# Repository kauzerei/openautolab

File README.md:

# OpenAutoLab

Free and open-source automatic film development machine.

[<br>Demo video](https://www.youtube.com/watch?v=Ryzbz89Sy8g)

OpenAutoLab is an attempt at making a cheap and simple film developing machine.
Inspired by Jobo Autolab, but cheaper, more repairable and open source.
Agitation is done by periodically moving fully submerged film, not rotating the drum constantly, so it is also more flexible, as it supports black-and-white processes.

Please take a look at the [OpenAutoLab documentation](https://kauzerei.github.io/openautolab/) for build and usage instructions.

- [Parts](https://kauzerei.github.io/openautolab/parts.html) contains information about all used electronic and mechanical components.
- [Build Instructions](https://kauzerei.github.io/openautolab/build_instructions.html) explains how to build the machine from scratch.
  - [Main Board](https://kauzerei.github.io/openautolab/main_board.html) concentrates on main board schematics and PCB layouts.
  - [Arduino Code](https://kauzerei.github.io/openautolab/arduino_code.html) contains build instructions for the source code of the controller of the machine.
- [Usage Instructions](https://kauzerei.github.io/openautolab/usage_instructions.html) explains how to use the finished machine.
- [Web Updater](https://kauzerei.github.io/openautolab/web_update.html) allows firmware upgrades on the main board.

You can find the latest released STL files and firmware binaries on the [GitHub releases page](https://github.com/kauzerei/openautolab/releases).

# Disclaimer

I do not take any responsibility for any damage done by mishandling chemicals.

For most processes rubber gloves suffice to keep you safe, but please refer to documents provided with each chemical you use, some are more toxic than others. This document explains the details of using the machine itself, without much attention towards the handling of chemicals. Research online if you are unsure, use your brain and be safe.

# License

The firmware, the design of 3d-printable files, the hardware design are licensed as GPLv3.
The firmware links to Arduino Servo library which is licensed under LGPL-2.1, LiquidCrystal I2C by Frank de Brabander which is licensed under LGPL-2.1, the HX711 by Bogdan Necula which is licensed under MIT.
For generation of 3d-printable .stl files Openscad is used, which is licensed under GPLv2.
The project also uses avrgirl-arduino licensed under MIT and zip.js licensed under BSD for the possibility of flashing from browser.

    This program is free software: you can redistribute it and/or modify
    it under the terms of the GNU General Public License as published by
    the Free Software Foundation, either version 3 of the License, or
    (at your option) any later version.

    This program is distributed in the hope that it will be useful,
    but WITHOUT ANY WARRANTY; without even the implied warranty of
    MERCHANTABILITY or FITNESS FOR A PARTICULAR PURPOSE. See the
    GNU General Public License for more details.

    You should have received a copy of the GNU General Public License
    along with this program. If not, see <https://www.gnu.org/licenses/>.

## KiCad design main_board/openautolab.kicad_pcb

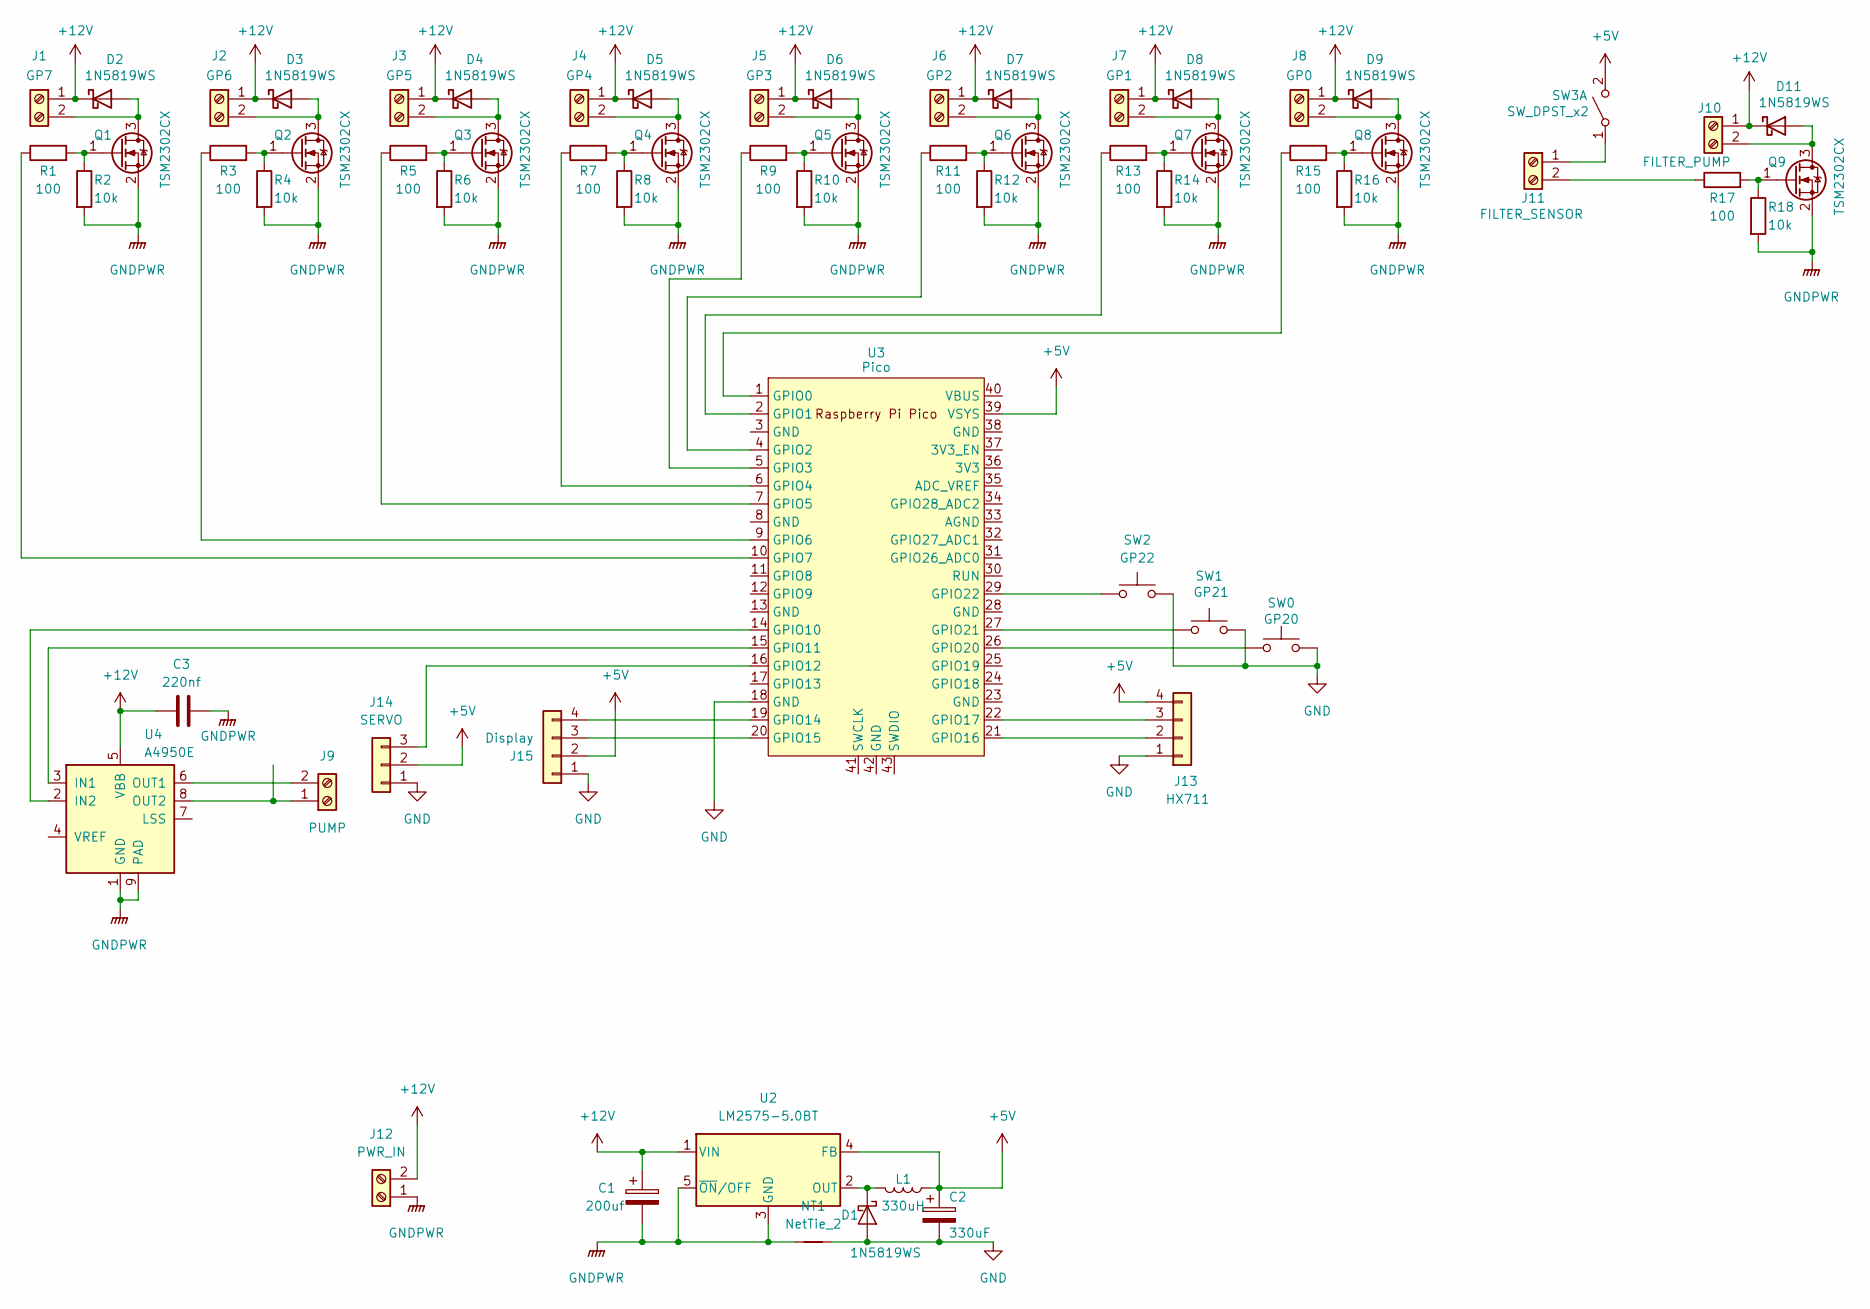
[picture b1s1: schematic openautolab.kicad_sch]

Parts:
C1: 200uf; CP_Elec_10x10; LCSC C125977
C2: 330uF; CP_Elec_6.3x7.7; LCSC C7471878
C3: 220nf; C_0805_2012Metric; LCSC C5378
D1, D2, D3, D4, D5, D6, D7, D8, D9, D11: 1N5819WS; D_SOD-323
J1: GP7; TerminalBlock_Phoenix_PT-1,5-2-3.5-H_1x02_P3.50mm_Horizontal
J2: GP6; TerminalBlock_Phoenix_PT-1,5-2-3.5-H_1x02_P3.50mm_Horizontal
J3: GP5; TerminalBlock_Phoenix_PT-1,5-2-3.5-H_1x02_P3.50mm_Horizontal
J4: GP4; TerminalBlock_Phoenix_PT-1,5-2-3.5-H_1x02_P3.50mm_Horizontal
J5: GP3; TerminalBlock_Phoenix_PT-1,5-2-3.5-H_1x02_P3.50mm_Horizontal
J6: GP2; TerminalBlock_Phoenix_PT-1,5-2-3.5-H_1x02_P3.50mm_Horizontal
J7: GP1; TerminalBlock_Phoenix_PT-1,5-2-3.5-H_1x02_P3.50mm_Horizontal
J8: GP0; TerminalBlock_Phoenix_PT-1,5-2-3.5-H_1x02_P3.50mm_Horizontal
J9: PUMP; TerminalBlock_Phoenix_MKDS-3-2-5.08_1x02_P5.08mm_Horizontal
J10: FILTER_PUMP; TerminalBlock_Phoenix_MKDS-3-2-5.08_1x02_P5.08mm_Horizontal
J11: FILTER_SENSOR; TerminalBlock_Phoenix_MKDS-3-2-5.08_1x02_P5.08mm_Horizontal
J12: PWR_IN; TerminalBlock_Phoenix_MKDS-3-2-5.08_1x02_P5.08mm_Horizontal
J13: HX711; PinSocket_1x04_P2.54mm_Vertical
J14: SERVO; PinSocket_1x03_P2.54mm_Vertical
J15: Display; PinSocket_1x04_P2.54mm_Vertical
L1: 330uH; L_12x12mm_H8mm; LCSC C10152
NT1: NetTie_2; NetTie-2_SMD_Pad0.5mm
Q1, Q2, Q3, Q4, Q5, Q6, Q7, Q8, Q9: TSM2302CX; SOT-23
R1, R3, R5, R7, R9, R11, R13, R15, R17: 100; R_0603_1608Metric
R2, R4, R6, R8, R10, R12, R14, R16, R18: 10k; R_0603_1608Metric
SW0: GP20; SW_SPST_B3S-1000
SW1: GP21; SW_SPST_B3S-1000
SW2: GP22; SW_SPST_B3S-1000
SW3: SW_DPST_x2; SW-SMD_6P-L5.8-W5.8-P2.00-LS8.0_YTSPS-22E58LM; LCSC C2941005
U2: LM2575-5.0BT; TO-263-5_TabPin3
U3: Pico; RPi_Pico_SMD_TH
U4: A4950E; SOIC-8-1EP_3.9x4.9mm_P1.27mm_EP2.41x3.3mm

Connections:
+5V: C2.1, J13.4, J14.2, J15.2, L1.1, SW3.2 (B), U2.4 (FB), U3.39 (VSYS)
+12V: C1.1, C3.1, D2.1 (K), D3.1 (K), D4.1 (K), D5.1 (K), D6.1 (K), D7.1 (K), D8.1 (K), D9.1 (K), D11.1 (K), J1.1, J2.1, J3.1, J4.1, J5.1, J6.1, J7.1, J8.1, J10.1, J12.2, U2.1 (VIN), U4.5 (VBB)
GND: C2.2, D1.2 (A), J13.1, J14.1, J15.1, NT1.2, SW0.2, SW1.2, SW2.2, U3.18 (GND)
GNDPWR: C1.2, C3.2, J12.1, NT1.1, Q1.2 (S), Q2.2 (S), Q3.2 (S), Q4.2 (S), Q5.2 (S), Q6.2 (S), Q7.2 (S), Q8.2 (S), Q9.2 (S), R2.2, R4.2, R6.2, R8.2, R10.2, R12.2, R14.2, R16.2, R18.2, U2.3 (GND), U2.5 (~ON/OFF), U4.1 (GND), U4.9 (PAD)
unnamed: D1.1 (K), L1.2, U2.2 (OUT)
unnamed: D2.2 (A), J1.2, Q1.3 (D)
unnamed: D3.2 (A), J2.2, Q2.3 (D)
unnamed: D4.2 (A), J3.2, Q3.3 (D)
unnamed: D5.2 (A), J4.2, Q4.3 (D)
unnamed: D6.2 (A), J5.2, Q5.3 (D)
unnamed: D7.2 (A), J6.2, Q6.3 (D)
unnamed: D8.2 (A), J7.2, Q7.3 (D)
unnamed: D9.2 (A), J8.2, Q8.3 (D)
unnamed: D11.2 (A), J10.2, Q9.3 (D)
unnamed: J9.1, U4.8 (OUT2)
unnamed: J9.2, U4.6 (OUT1)
unnamed: J11.1, SW3.1 (A)
unnamed: J11.2, R17.1
unnamed: J13.2, U3.21 (GPIO16)
unnamed: J13.3, U3.22 (GPIO17)
unnamed: J14.3, U3.16 (GPIO12)
unnamed: J15.3, U3.20 (GPIO15)
unnamed: J15.4, U3.19 (GPIO14)
unnamed: Q1.1 (G), R1.2, R2.1
unnamed: Q2.1 (G), R3.2, R4.1
unnamed: Q3.1 (G), R5.2, R6.1
unnamed: Q4.1 (G), R7.2, R8.1
unnamed: Q5.1 (G), R9.2, R10.1
unnamed: Q6.1 (G), R11.2, R12.1
unnamed: Q7.1 (G), R13.2, R14.1
unnamed: Q8.1 (G), R15.2, R16.1
unnamed: Q9.1 (G), R17.2, R18.1
unnamed: R15.1, U3.1 (GPIO0)
unnamed: R13.1, U3.2 (GPIO1)
unnamed: R11.1, U3.4 (GPIO2)
unnamed: R9.1, U3.5 (GPIO3)
unnamed: R7.1, U3.6 (GPIO4)
unnamed: R5.1, U3.7 (GPIO5)
unnamed: R3.1, U3.9 (GPIO6)
unnamed: R1.1, U3.10 (GPIO7)
unnamed: U3.14 (GPIO10), U4.2 (IN2)
unnamed: U3.15 (GPIO11), U4.3 (IN1)
unnamed: SW0.1, U3.26 (GPIO20)
unnamed: SW1.1, U3.27 (GPIO21)
unnamed: SW2.1, U3.29 (GPIO22)

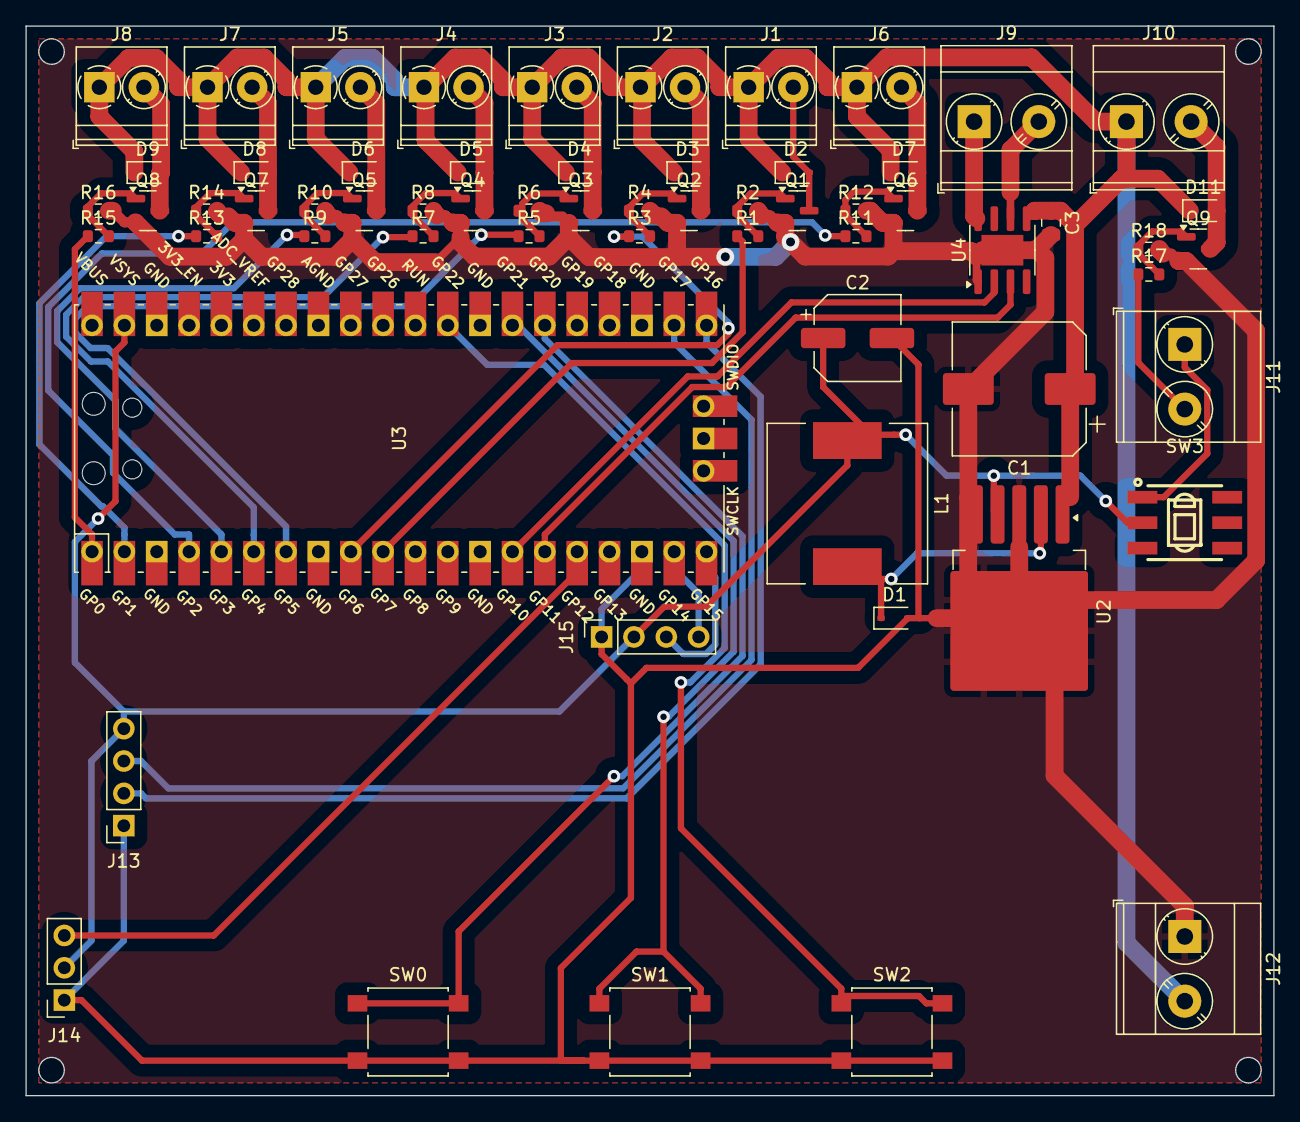
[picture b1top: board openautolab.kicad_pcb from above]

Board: 2 copper layers, 98.0 x 84.0 mm, 64 parts (0 on the bottom side), 45 nets.

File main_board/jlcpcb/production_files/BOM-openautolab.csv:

Comment,Designator,Footprint,LCSC,Quantity
330uH,L1,L_12x12mm_H8mm,C10152,1
200uf,C1,CP_Elec_10x10,C125977,1
1N5819WS,"D1,D2,D3,D4,D5,D6,D7,D8,D9",D_SOD-323,C191023,9
100,"R1,R10,R11,R12,R13,R14,R15,R16,R17,R18,R2,R3,R4,R5,R6,R7,R8,R9",R_0603_1608Metric,C25804,18
SW_DPST_x2,SW3,SW-SMD_6P-L5.8-W5.8-P2.00-LS8.0_YTSPS-22E58LM,C2941005,1
TSM2302CX,"Q1,Q2,Q3,Q4,Q5,Q6,Q7,Q8,Q9",SOT-23,C2977534,9
LM2575-5.0BT,U2,TO-263-5_TabPin3,C347405,1
GP20,"SW0,SW1,SW2",SW_SPST_B3S-1000,C455110,3
220nf,C3,C_0805_2012Metric,C5378,1
330uF,C2,CP_Elec_6.3x7.7,C7471878,1
A4950E,U4,SOIC-8-1EP_3.9x4.9mm_P1.27mm_EP2.41x3.3mm,C7473144,1
1N5819WS,D11,D_SOD-323,,1

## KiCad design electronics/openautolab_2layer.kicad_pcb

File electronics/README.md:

# Parts list, electronic schematics, PCB layouts.
## Schematics and PCB layouts
Schematics and PCB layouts are stored in KiCAD 6.0 format. `openautolab_2layer.kicad_pcb` is automatically routed double-layered version of the board with plated through holes aimed at having it produced by professionals.  
`openautolab.kicad_pcb` is hand-routed single-layer version, optimized for DIY production at home. Jumper wires on signal lines could be avoided by routing some tracks between pads, but it requires better precision than toner transfer technique can provide. Two jumper wires on power lines however are a necessity.  
## List of components to buy
### Main board
- Arduino Nano
- Mini 360 buck converter, or any suitable 5v converter
- 12mm buzzer
- 5 flyback diodes, for example 1N4004, but almost any diode will do
- 10 screw terminal blocks, for example Phoenix MKDS 3/ 2-5.08 1x2
- 3 6x6mm push switches 
- 2 12VDC relays, for example SRD-12VDC-SL-C or Finder 36.11.9.012
- 2 darlington transistor arrays TD62064APG
- SPDT ON-ON (or SPST) toggle switch with 5.08mm raster, for example APEM 5026
- 3x1 pin header for connecting servo
- 2 4x1 socket header for connecting display and scale 
Feel free to modify the PCB to fit available components, like changing footprint for different pump switch or DC-DC converter. 
### Electromechanics
- 4-6 normally-closed 12V valves. See the picture as a reference, those are cheap and good enough. Number of valves depends on what process you want to run. 1 valve for water, 1 valve for waste, plus 1 valve for each chemical. 4 in total fro black&white, 5 for c41, 6 for e6.
- ZC-A210 or similar 12V gear pump, capable of running in two directions at a speed of about 2l/min for prolonged times.
- Weight cell and HX711 ADC for it.
- MG90 servo
Optional: 
- Brita filter for water
- Any pump that can work for prolonged periods without overheating
- Float switch
### Other parts to buy
- Flexible hose. The choice depends on the pump and valves, 6mm inner diameter seems to work.
- 3-5 Y-pipes or T-pipes, one for each valve minus one.
- Developing tank. AP developing tank is recommended
- Beakers for chemicals
Optional:
Sous Vide and come water-tight container for heating the beakers with water.
## Problems to solve
1. Developing tank needs to be connected to the hose and to be somehow agitated. Those problems could be solved in a number of ways, I suggest the following way. Drill a hole in a bottom of the tank and insert a hose adapter with built-in light trap, which lets liquids through, but does not let the light in. Agitate using agitation rod attached to servo. In the `mechanics` subdirectory there are part desidns of a light-tight adapter and servo-powered agitator compatible with AP developing tank. Parts compatible with other tanks should be designed individually for each one.

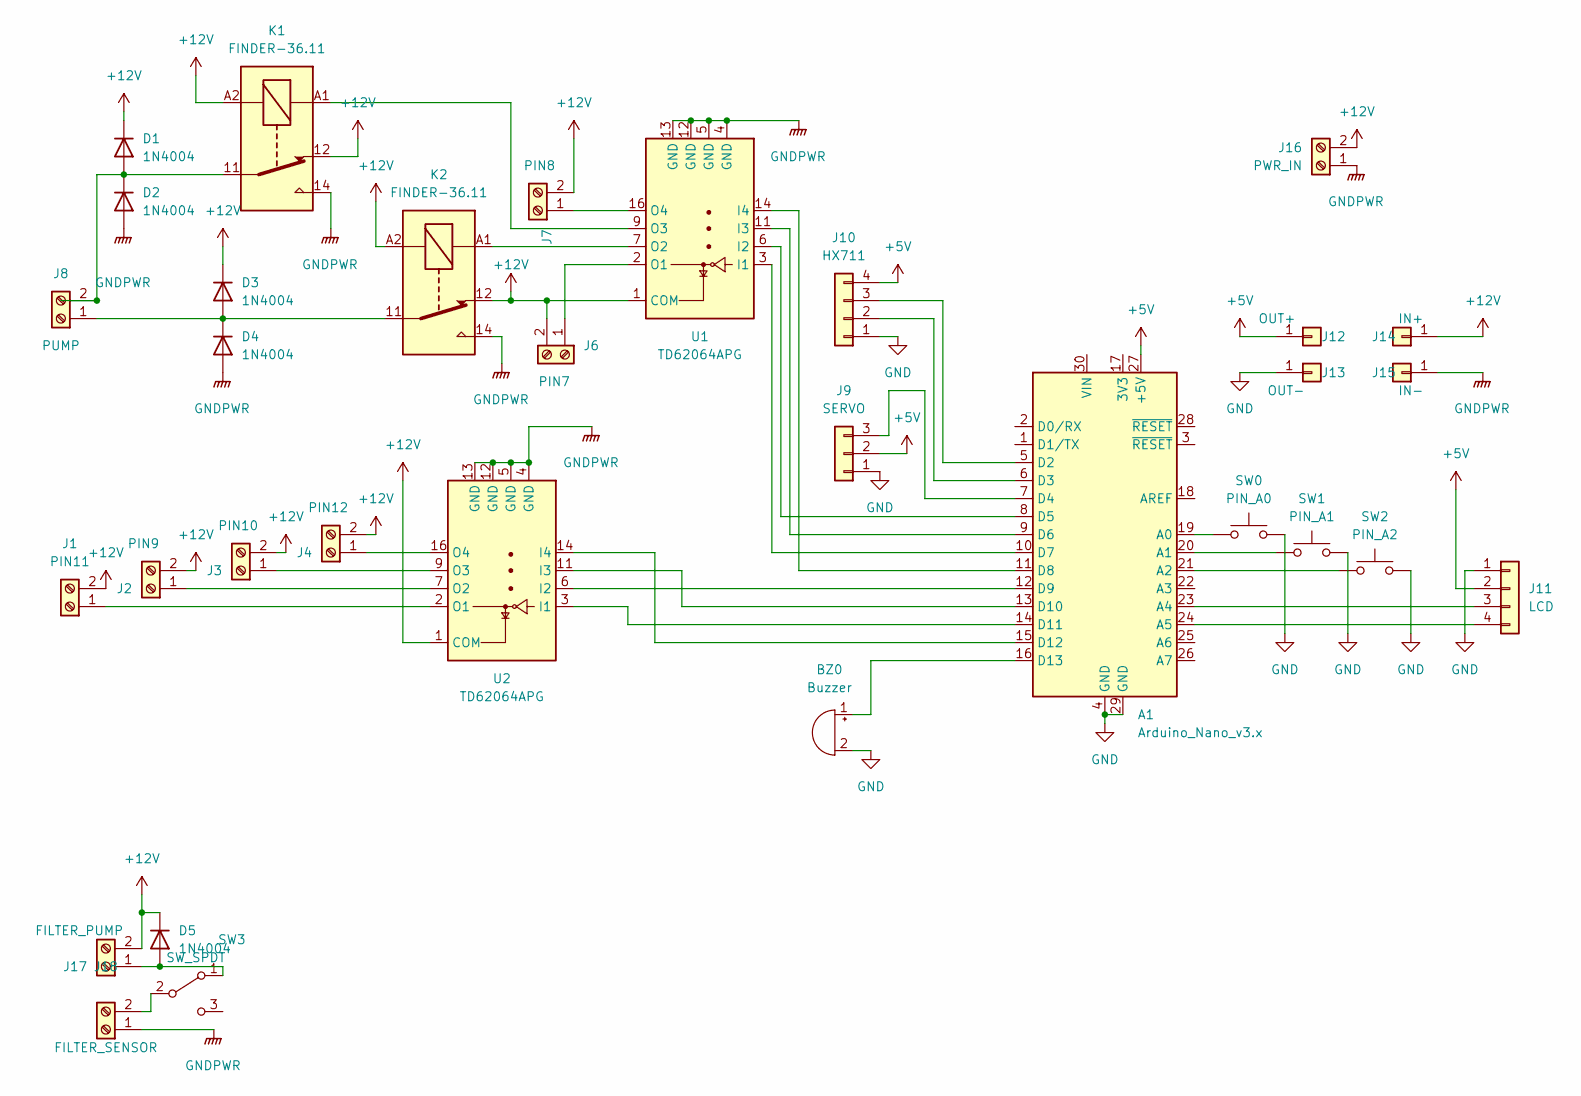
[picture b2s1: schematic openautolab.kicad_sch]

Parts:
A1: Arduino_Nano_v3.x; Arduino_Nano
BZ0: Buzzer; Buzzer_12x9.5RM7.6
D1, D2, D3, D4, D5: 1N4004; D_DO-41_SOD81_P10.16mm_Horizontal
J1: PIN11; TerminalBlock_Phoenix_MKDS-3-2-5.08_1x02_P5.08mm_Horizontal
J2: PIN9; TerminalBlock_Phoenix_MKDS-3-2-5.08_1x02_P5.08mm_Horizontal
J3: PIN10; TerminalBlock_Phoenix_MKDS-3-2-5.08_1x02_P5.08mm_Horizontal
J4: PIN12; TerminalBlock_Phoenix_MKDS-3-2-5.08_1x02_P5.08mm_Horizontal
J6: PIN7; TerminalBlock_Phoenix_MKDS-3-2-5.08_1x02_P5.08mm_Horizontal
J7: PIN8; TerminalBlock_Phoenix_MKDS-3-2-5.08_1x02_P5.08mm_Horizontal
J8: PUMP; TerminalBlock_Phoenix_MKDS-3-2-5.08_1x02_P5.08mm_Horizontal
J9: SERVO; PinSocket_1x03_P2.54mm_Vertical
J10: HX711; PinSocket_1x04_P2.54mm_Vertical
J11: LCD; PinSocket_1x04_P2.54mm_Vertical
J12: OUT+; PinHeader_1x01_P2.54mm_Vertical
J13: OUT-; PinHeader_1x01_P2.54mm_Vertical
J14: IN+; PinHeader_1x01_P2.54mm_Vertical
J15: IN-; PinHeader_1x01_P2.54mm_Vertical
J16: PWR_IN; TerminalBlock_Phoenix_MKDS-3-2-5.08_1x02_P5.08mm_Horizontal
J17: FILTER_PUMP; TerminalBlock_Phoenix_MKDS-3-2-5.08_1x02_P5.08mm_Horizontal
J18: FILTER_SENSOR; TerminalBlock_Phoenix_MKDS-3-2-5.08_1x02_P5.08mm_Horizontal
K1, K2: FINDER-36.11; Relay_SPDT_Finder_36.11
SW0: PIN_A0; SW_PUSH_6mm
SW1: PIN_A1; SW_PUSH_6mm
SW2: PIN_A2; SW_PUSH_6mm
SW3: SW_SPDT; SW_Slide_1P2T_CK_OS102011MS2Q
U1, U2: TD62064APG; DIP-16_W7.62mm

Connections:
+5V: A1.27 (+5V), J9.2, J10.4, J11.2, J12.1
+12V: D1.1 (K), D3.1 (K), D5.1 (K), J1.2, J2.2, J3.2, J4.2, J6.2, J7.2, J14.1, J16.2, J17.2, K1.12, K1.A2, K2.12, K2.A2, U1.1 (COM), U2.1 (COM)
GND: A1.4 (GND), A1.29 (GND), BZ0.2 (+), J9.1, J10.1, J11.1, J13.1, SW0.2, SW1.2, SW2.2
GNDPWR: D2.2 (A), D4.2 (A), J15.1, J16.1, J18.1, K1.14, K2.14, U1.4 (GND), U1.5 (GND), U1.12 (GND), U1.13 (GND), U2.4 (GND), U2.5 (GND), U2.12 (GND), U2.13 (GND)
unnamed: A1.5 (D2), J10.3
unnamed: A1.6 (D3), J10.2
unnamed: A1.7 (D4), J9.3
unnamed: A1.8 (D5), U1.6 (I2)
unnamed: A1.9 (D6), U1.11 (I3)
unnamed: A1.10 (D7), U1.3 (I1)
unnamed: A1.11 (D8), U1.14 (I4)
unnamed: A1.12 (D9), U2.6 (I2)
unnamed: A1.13 (D10), U2.11 (I3)
unnamed: A1.14 (D11), U2.3 (I1)
unnamed: A1.15 (D12), U2.14 (I4)
unnamed: A1.16 (D13), BZ0.1 (-)
unnamed: A1.19 (A0), SW0.1
unnamed: A1.20 (A1), SW1.1
unnamed: A1.21 (A2), SW2.1
unnamed: A1.23 (A4), J11.3
unnamed: A1.24 (A5), J11.4
unnamed: D1.2 (A), D2.1 (K), J8.2, K1.11
unnamed: D3.2 (A), D4.1 (K), J8.1, K2.11
unnamed: D5.2 (A), J17.1, SW3.1 (A)
unnamed: J1.1, U2.2 (O1)
unnamed: J2.1, U2.7 (O2)
unnamed: J3.1, U2.9 (O3)
unnamed: J4.1, U2.16 (O4)
unnamed: J6.1, U1.2 (O1)
unnamed: J7.1, U1.16 (O4)
unnamed: J18.2, SW3.2 (B)
unnamed: K1.A1, U1.9 (O3)
unnamed: K2.A1, U1.7 (O2)

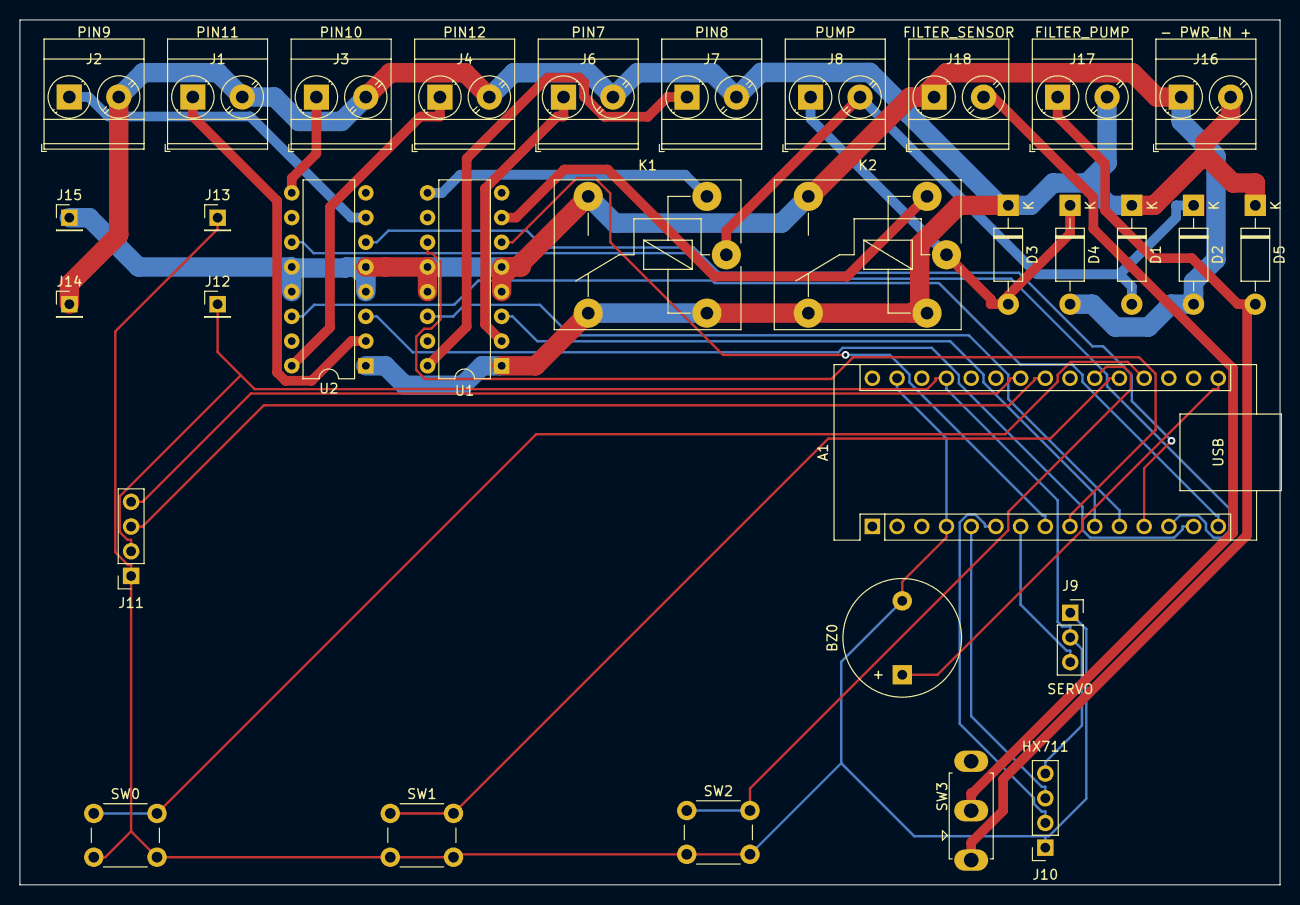
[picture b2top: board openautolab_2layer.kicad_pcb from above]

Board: 2 copper layers, 129.5 x 88.9 mm, 32 parts (0 on the bottom side), 33 nets.

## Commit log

2023-01-29 some initial files
2023-01-29 add 2-layer version of the board
2023-01-29 start list of parts
2023-01-29 remove kicad backup files
2023-01-29 more hardware readme
2023-01-29 project structure reorganization
2023-01-29 upload source code for LED version
2023-01-29 start rewriting code. correct pin numbers
2023-01-29 add dependencies
2023-01-29 migrated from led to lcd display
2023-01-29 menu items placeholders
2023-01-29 start 3d designing
2023-01-29 add some 3d modeling drafts
2023-01-29 new draft for 3dprinted parts
2023-01-29 correctly shaped cavity inside adapter, main non-light-tight part almost ready
2023-01-29 openscad file refinement
2023-01-29 remove unnecessary scad files
2023-01-29 main_body of scad file is ready
2023-01-29 top screw and main magnet cover ready
2023-01-29 hose adapter ready
2023-01-29 proper formula for thread diameter from rod diameter
2023-01-29 add magnetic holder
2023-01-29 start final assembly visualization
2023-01-29 3d model seems right, not going to optimize and refine any time soon
2023-02-06 better work with tolerances
2023-02-08 start writing display time visualization functions
2023-02-08 better hose adapter
2023-02-13 start threaded-rod frame design
2023-02-13 add top corner
2023-02-13 frame size calculation
2023-02-14 frame assembly (for visualization)
2023-02-14 mounting blocks
2023-02-16 valve holders
2023-02-16 attachments for magnetic holders
2023-02-18 add threading helping instrument
2023-02-18 attempt at adding side thread cutting helper. no air gap and ugly
2023-02-18 better threading helper, still unfinished
2023-02-18 tap helpers all correctly generated. outer thread to go
2023-02-19 deuglify 2d projection and minkowski call
2023-02-19 small changes in numbers
2023-02-19 holes for handles for helper
2023-02-19 hexagonal hollow screw head
2023-02-20 fix rounding error, causing helper tool to fail on large offsets. minor changes in rotating main_body
2023-02-20 beautify code. i mean, indentation and stuff, the code itself is still ugly
2023-02-20 die holder
2023-02-20 added weight gauge mount
2023-02-20 wrenches for the wrench god
2023-02-21 weight gauge mount to rods
2023-02-21 magic numbers
2023-02-21 better wrench
2023-02-23 pump holder and started new frame
2023-02-24 new better frame
2023-02-24 start tank adapters
2023-02-25 better coupling for the rod
2023-02-26 add testing gauge for servo mount
2023-02-26 modify tank agitation mount
2023-03-07 start pcb cover
2023-03-07 parametric pcb box
2023-03-07 remove kicad backups, edit gitignore to ignore backups
2023-03-10 frame upgrades
2023-03-12 add printable buttons
2023-03-13 some code reorganizing
2023-03-17 changes in lcd interface
2023-03-17 placeholders for all states
2023-03-17 fix indentation
2023-03-17 most settings done
2023-03-17 almost all settings done. Key repeat where needed
2023-03-17 small bugfixes
2023-03-17 parameters stored in eeprom
2023-03-17 remove tmp file
2023-03-18 some logic is done, some placeholders are written
2023-03-18 correct display of process
2023-03-18 data structures ready, bw process works, placeholders instead of pumping and agitating
2023-03-19 implemented key repeat
2023-03-19 used key repeat everywhere it's possible
2023-03-20 switch to a better hx711 library. Implement calibration
2023-03-20 scale calibration stored in eeprom
2023-03-21 agitation done
2023-03-21 avoid string operations
2023-03-21 move large string constants to progmem
2023-03-21 fix film count
2023-03-29 reworking threads
2023-03-31 rework threaded parts
2023-03-31 fix threaded parts, add thread fit debugging tool
2023-03-31 fix magnet fitting
2023-04-01 perpendicular weight gauge mount
2023-04-07 fix horizzontal walls, fix weight gauge mount
2023-04-10 used legacy pump code. too lazy to implement anything better
2023-04-10 add filter pump holder
2023-04-15 add holder for magnetic filter fill sensor
2023-05-01 some build instructions
2023-05-06 more build instructions
2023-05-12 more building instructions
2023-05-12 printing advices
2023-05-13 finish printing advices
2023-05-13 start scad parameter guide
2023-05-14 fix vertical positions and sizes of bodies in interfaces
2023-05-14 small fixes in models. model modification instructions
2023-05-14 add more scad parameter descriptions
2023-05-14 finish scad parameter description
2023-05-20 pump out withought weight threshold. Air pumping limit longer
2023-05-20 update PCB
2023-05-20 adapt front panel to new pcb
2023-05-27 update pump holder. small part to mount pcb on the top rod
2023-06-01 wrench tool
2023-06-17 redesign front panel
2023-06-17 fix bug in board mounts. update dimensions
2023-06-17 fix button sizes
2023-07-01 correct c41, cleaning fucntions
2023-07-04 remake frame according to KISS principle
2023-07-16 fix cleaning code
2023-07-16 fix frame
2023-07-20 add filter support
2023-07-23 cleanup. beautify code, reorganize modules in files
2023-07-23 fix filter support size
2023-07-23 fix some default values
2023-07-23 wg mount slots for better alignment
2023-07-30 fix folder structure in arduino_code
2023-07-30 improve menu
2023-07-30 fix service messages
2023-07-30 fix logic in cleaning
2023-08-11 update documentatui
2023-08-12 update documentation to reflect newer frame design
2023-08-12 update build instructions: mounting electronics
2023-08-12 update instructions. Change build order.
2023-09-01 restore erroneously deleted pcb holder
2023-09-01 restore erroneously deleted nut spinner
2023-09-01 different filter pump types
2023-09-01 cleanup
2023-09-02 renaming reorganizing
2023-09-05 make names of parts consistent throughout scad files and building.md, better build description, scad files cleanup
2023-09-06 stl generator for mac, cleanup in parts names
2023-09-06 optional tools separately
2023-09-08 memory tracking runction, add beep
2023-09-08 fix some of stl-generation errors
2023-09-08 fix the rest of stl-generation (for mac)
2023-09-08 start better parts list
2023-09-08 better tables for frame, picture descriptions to shoot
2023-09-08 better tables for frame, picture descriptions to shoot, up to PCB attachment
2023-09-08 better tables for frame, picture descriptions to shoot done
2023-09-09 makind parts updated, relative links between documents
2023-09-09 fix capitalization
2023-09-09 fixing build instructions as i shoot photos
2023-09-10 update scad parameter description
2023-09-11 small fixes in documentation, mostly markdown-related
2023-09-11 typo
2023-09-11 improving instructions while making build photots
2023-09-12 fix build instructions while making build pictures
2023-09-30 manual with pictures
2023-09-30 debug instructions
2023-10-01 update schematic add power switch
2023-10-01 enclosure holes
2023-10-01 some improvements in parts, regenerated stls
2023-10-03 remove ds store
2023-10-03 update gitignore
2023-10-10 fix display size
2023-10-11 small change in pcb holder
2023-12-14 some hardware-debuggigng code
2023-12-14 start reorganizing states
2023-12-17 code reorganization
2023-12-27 tank weignt bug fix
2023-12-27 modify readme
2023-12-28 test gh pages deploy
2023-12-28 fix links, add mainboard page
2023-12-28 slightly clean up markdown to render tables
2023-12-28 default to light theme always. add github and edit links.
2023-12-29 markdown fixes
2023-12-29 tweak docs
2023-12-29 test compile workflow
2023-12-29 retry workflow
2023-12-29 retry workflow lib
2023-12-29 retry workflow path
2023-12-29 retry workflow checkout
2023-12-29 retry workflow checkout path
2023-12-29 retry workflow path again
2023-12-29 checkout v3
2023-12-29 try to upload build artifact
2023-12-29 try short arg
2023-12-29 flags as list
2023-12-29 flags as seen elsewhere
2023-12-29 artifact path
2023-12-29 add youtube video embed
2023-12-29 fix youtube in readme
2024-01-01 try to generate stls with github actions
2024-01-01 fix artifact upload for scad rendering
2024-01-01 try auto upload for new releases
2024-01-01 retry release upload
2024-01-01 retry with new artifact paths
2024-01-02 add web flashing utility
2024-01-02 submodules in workflows
2024-01-02 tweak permission on github workflows
2024-01-04 some cleanup after filming, removed timer hacks
2024-01-05 add license, update video, add email
2024-01-06 usage instructions and disclaimers
2024-01-06 fix video
2024-01-06 secret menu and picture
2024-01-06 fixed power switch on board
2024-01-06 update fabrication files
2024-01-09 made frame stronger
2024-01-09 remove pcb fabrication files
2024-01-09 generate pcb gerbers as github action
2024-01-17 update board
2024-01-25 saving progress
2024-02-03 update schematic, complete parts description
2024-02-03 reorganize instructions formatting, adding more text
2024-02-04 board bom
2024-02-04 smaller box
2024-02-05 restore erroneously deleted script
2024-03-01 fixed error in board
2024-04-06 more accessible valves, small changes in enclosure
2024-04-19 valve holder rotated
2024-05-05 nut shape
2024-05-07 update models
2024-05-16 better bracket for battery and enclosure
2024-05-17 place for nuts
2024-05-17 fix bug in filling vessels
2024-05-27 main pump bracket was mirrored
2024-05-27 small bracket moved to frame
2024-05-27 remove traces of small bracket from upper rail
2024-05-28 move battery enclosure to enclosure
2024-05-28 variable naming consistancy
2024-05-29 module naming consistency
2024-05-29 parameter naming consistency
2024-05-29 some nuances in docs
2024-06-15 add pictures
2024-06-19 added ruler for scale
2024-06-19 add ground plane
2024-06-19 update pictures in docs
2024-06-21 update fabrication builder
2024-06-28 some valve debugging code
2024-06-28 some cleanup in instructions
2024-06-28 finished cleaning text of instructions
2024-06-29 fix instruction pictures
2024-06-29 clean up code a little
2024-07-05 fix pictures
2024-07-05 doc cleanup
2024-07-05 hotfix screws sizes and bom
2024-07-05 hotfix kicad version
2024-10-23 update schematic
2024-10-25 all footprints correct except toggle switch
2024-10-25 fix footprints
2024-10-25 all footprints correct. draft of a layout
2024-10-25 prepare for routing
2024-10-29 really prepared for routing
2024-10-29 routing done
2024-11-01 minor routing-related stuff
2025-12-08 3d design tweaks
2025-12-08 started with pico based code
2025-12-08 did i fix the submodule thingy?
